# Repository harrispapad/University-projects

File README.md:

# University Projects

This repository contains coursework and projects from my Electrical and Computer Engineering studies at the National Technical University of Athens (NTUA). Each directory represents a different course with assignments, lab work, and projects.

## 📚 Course Overview

### Computer Architecture & Systems

#### [Advanced Computer Architecture](Advanced%20Computer%20Architecture/)

Advanced topics in computer architecture including branch prediction algorithms and memory hierarchy optimization using Intel Pin tools and SPEC CPU2006 benchmarks.

#### [Computer Architecture](Computer%20Architecture/)

Fundamental and advanced computer architecture concepts including ISA, pipelining, cache design, and multiprocessor systems.

#### [Advanced Operational Systems](Advanced%20Operational%20Systems/)

Linux kernel programming, device drivers (LUNIX TNG sensor driver), and system-level programming.

#### [Operational Systems](Operational%20Systems/)

Unix/Linux system programming, process management, POSIX threads, and synchronization primitives.

### VLSI & Hardware Design

#### [Analog VLSI](Analog%20VLSI/)

Analog Bayesian classifier circuit design with winner-take-all circuits, current mirrors, and performance analysis.

#### [Analog System Design](Analog%20System%20Design/)

Phase-Locked Loop (PLL) circuit design with LTspice simulations and KiCad PCB implementation.

#### [Digital VLSI](Digital%20VLSI/)

FPGA design using Xilinx Vivado: decoders, shift registers, BCD adders, systolic multipliers, and Bayer demosaicing for image processing.

#### [Digital Systems Lab](Digital%20Systems%20Lab/)

Digital circuit design using Logisim: clock generators, display circuits, counters, and Pong display systems.

#### [Electrical Design](Electrical%20Design/)

Complete electrical installation design for multi-story buildings using AutoCAD, including floor plans, panel diagrams, and load calculations.

### Programming & Software

#### [Algorithms and Complexity](Algorithms%20and%20Complexity/)

Theoretical and programming assignments covering algorithm design, complexity analysis, graph algorithms, and competitive programming problems.

#### [Compilers](Compilers/)

Complete compiler implementation for the Dana programming language with lexer, parser, semantic analysis, and LLVM IR code generation.

#### [Databases](Databases/)

MasterChef competition management database with ER modeling, MySQL implementation, and automated data population scripts.

#### [Programming Languages](Programming%20Languages/)

Multi-paradigm programming comparing imperative (C/C++), object-oriented (Java), functional (Standard ML), logic (Prolog), and scripting (Python) approaches.

#### [Software Engineering](Software%20Engineering/)

Full-stack web application with Express.js backend, MySQL database, web frontend, and CLI client featuring JWT authentication.

#### [progintro](progintro/)

Introductory C programming: data structures, algorithms, and fundamental programming concepts.

#### [progtech](progtech/)

Advanced C++ programming with focus on STL (Standard Template Library) and object-oriented design.

### Microprocessors & Embedded Systems

#### [Intro to Microprocessors](Intro%20to%20Microprocessors/)

Assembly language programming for 8085 and AVR microprocessors using Atmel Studio.

#### [Microlab](Microlab/)

PIC18 microcontroller programming with MPLAB X: I2C/TWI communication, LCD interfaces, USART, and One-Wire protocols.

### AI & Machine Learning

#### [Neural Networks and Deep Learning](Neural%20Networks%20and%20Deep%20Learning/)

Deep learning implementations in Python/Jupyter: Wide Residual Networks, neural network architectures, and optimization techniques.

## 🛠️ Technologies & Tools

- **Languages**: C, C++, Java, Python, Standard ML, Prolog, VHDL, Assembly (8085, AVR, PIC18), JavaScript, SQL
- **Hardware Design**: Xilinx Vivado, LTspice, KiCad, Logisim, AutoCAD, Logisim
- **Development Tools**: Intel Pin, MPLAB X, Atmel Studio, MySQL Workbench
- **Frameworks**: Express.js, Node.js, LLVM, PyTorch/TensorFlow
- **Version Control**: Git

## 📁 Repository Structure

Each course directory contains:

- Assignment descriptions and requirements
- Source code and implementations
- Project reports and documentation
- Test cases and validation scripts
- Build configurations and makefiles

## 📖 Documentation

Each subdirectory has its own README with detailed information about:

- Course objectives and learning outcomes
- Assignment descriptions and solutions
- Implementation details and design decisions
- Tools and technologies used

## 🎓 Institution

**National Technical University of Athens (NTUA)**
School of Electrical and Computer Engineering

---

*This repository serves as a comprehensive portfolio of my academic work in Electrical and Computer Engineering.*

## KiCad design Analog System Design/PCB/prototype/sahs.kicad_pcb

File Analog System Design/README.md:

# Analog System Design

This directory contains the course project for Analog System Design, focused on designing and implementing a Phase-Locked Loop (PLL) system.

## Contents

### Project Overview

Design and implementation of a complete PLL (Phase-Locked Loop) circuit, including:

- VCO (Voltage-Controlled Oscillator) design
- Phase detector implementation
- Loop filter design
- Complete PLL system integration

**Partners:** Chronopoulos Stefanos, Gougousi Ioanna

Simulations (`simulations/`)

LTspice simulation files for circuit analysis and verification:

- VCO simulations and small-signal analysis
- Complete PLL system simulations
- Parametric sweeps and performance analysis
- Simulation logs and results documentation

### PCB Design (`PCB/`)

KiCad PCB design files for physical implementation:

- Custom component footprints for ICs (74HC00, 74HC14, 74HCT74, LM324) and transistors (2N2222, 2N2907)
- Schematic symbols library
- PCB layouts (prototype and final with switch)
- SPICE models for circuit simulation in KiCad

### Documentation

- **`report.pdf`**: Final project report

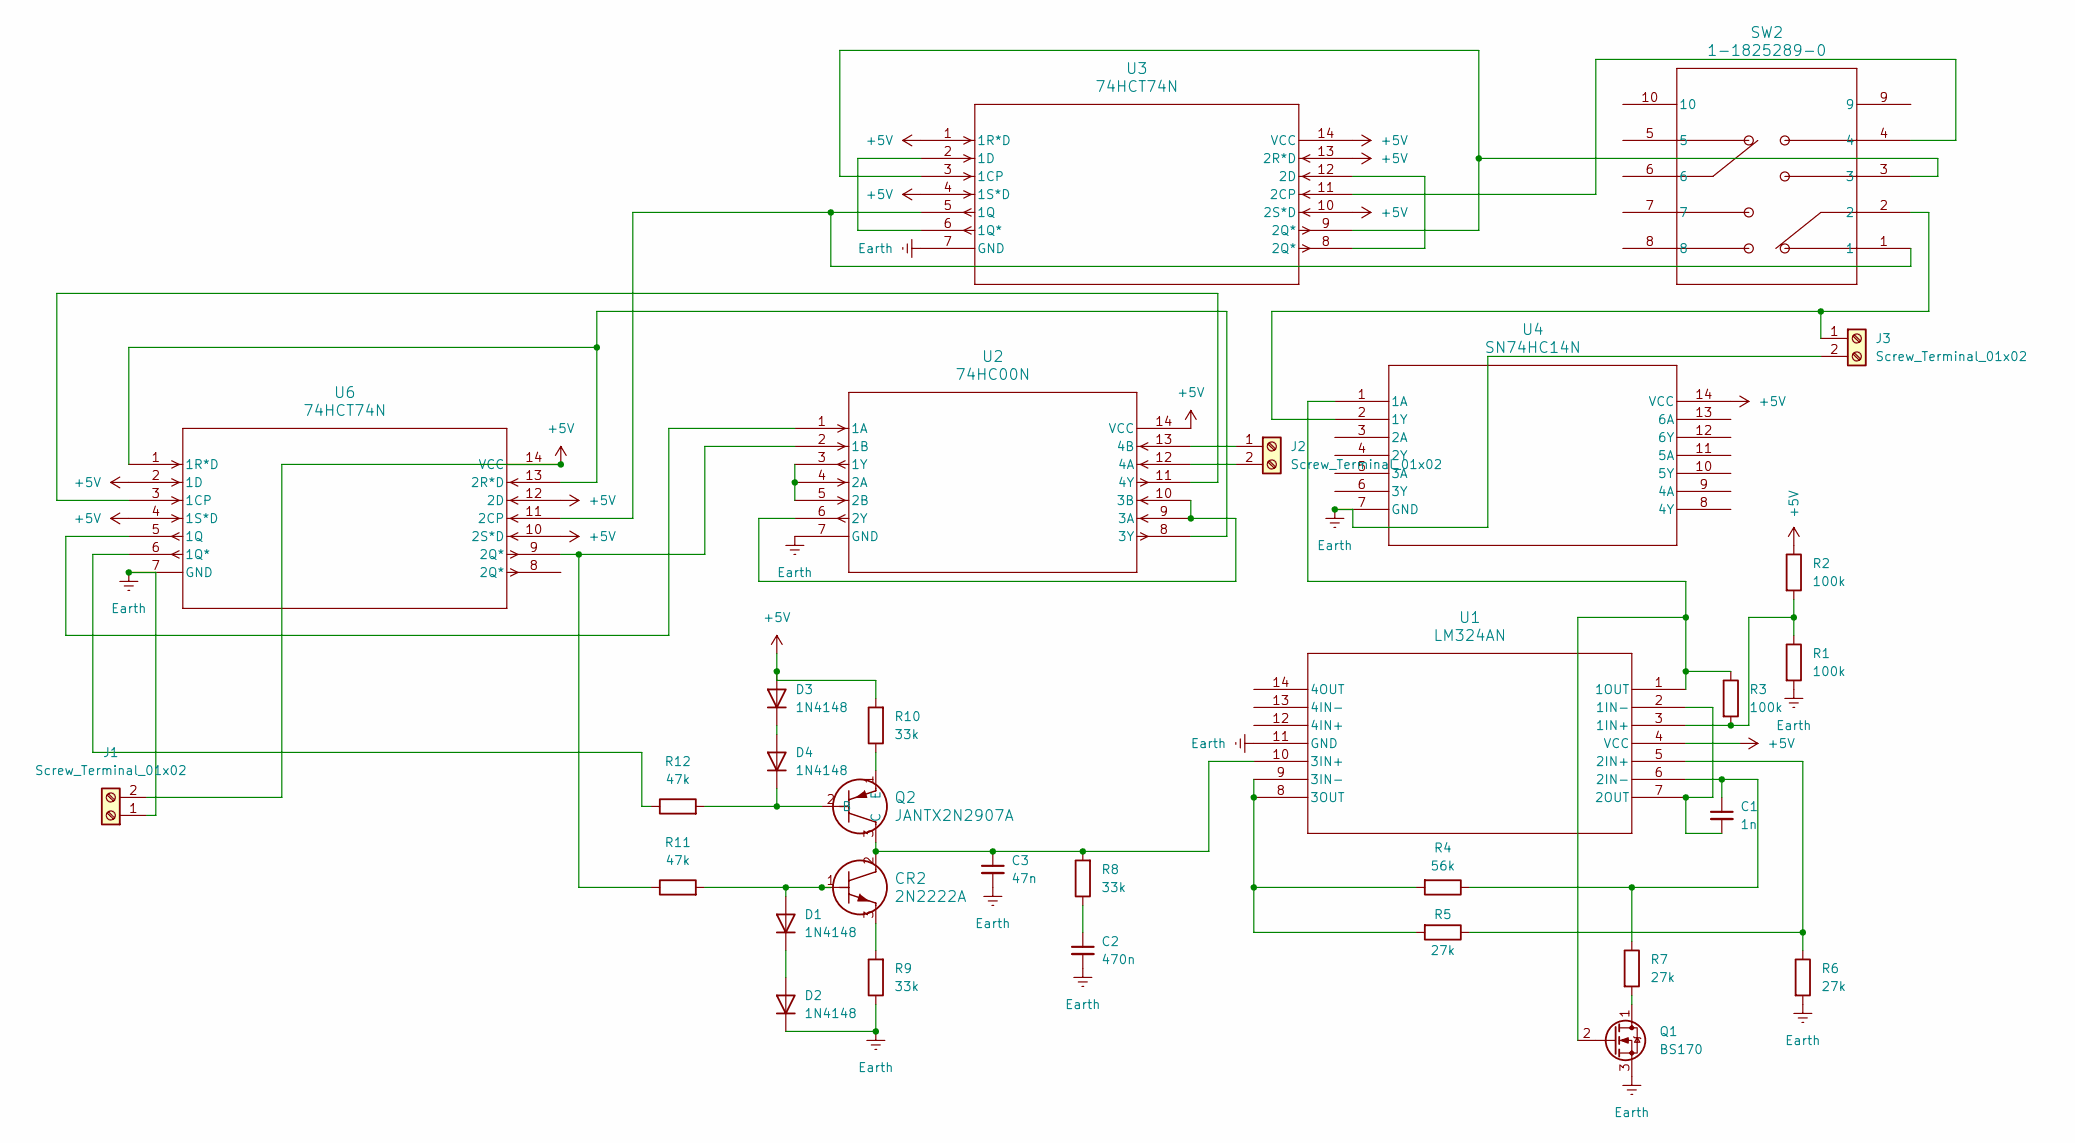
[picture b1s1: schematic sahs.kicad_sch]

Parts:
C1: 1n; C_Disc_D3.0mm_W1.6mm_P2.50mm
C2: 470n; C_Rect_L7.0mm_W6.0mm_P5.00mm
C3: 47n; C_Disc_D3.0mm_W1.6mm_P2.50mm
CR2: 2N2222A; TO-18_STM
D1, D2, D3, D4: 1N4148; D_DO-35_SOD27_P7.62mm_Horizontal
J1, J2, J3: Screw_Terminal_01x02; TerminalBlock_Altech_AK300-2_P5.00mm
Q1: BS170; TO-92_Inline
Q2: JANTX2N2907A; TO-18TO-206AA_MCH
R1, R2, R3: 100k; R_Axial_DIN0207_L6.3mm_D2.5mm_P7.62mm_Horizontal
R4: 56k; R_Axial_DIN0207_L6.3mm_D2.5mm_P7.62mm_Horizontal
R5, R6, R7: 27k; R_Axial_DIN0207_L6.3mm_D2.5mm_P7.62mm_Horizontal
R8, R9, R10: 33k; R_Axial_DIN0207_L6.3mm_D2.5mm_P7.62mm_Horizontal
R11, R12: 47k; R_Axial_DIN0207_L6.3mm_D2.5mm_P7.62mm_Horizontal
SW2: 1-1825289-0; SW8_MHS233_TEC
U1: LM324AN; N14
U2: 74HC00N; SOT27-1_NEX
U3, U6: 74HCT74N; SOT27-1_NEX
U4: SN74HC14N; N14

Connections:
+5V: D3.2 (A), J1.2, R2.1, R10.2, U1.4 (VCC), U2.14 (VCC), U3.1 (1R*D), U3.4 (1S*D), U3.10 (2S*D), U3.13 (2R*D), U3.14 (VCC), U4.14 (VCC), U6.2 (1D), U6.4 (1S*D), U6.10 (2S*D), U6.12 (2D), U6.14 (VCC)
Earth: C2.2, C3.2, D2.1 (K), J1.1, J3.2, Q1.3 (S), R1.2, R6.2, R9.1, U1.11 (GND), U2.7 (GND), U3.7 (GND), U4.7 (GND), U6.7 (GND); also elsewhere on the board
unnamed: C2.1, R8.1
unnamed: CR2.3, R9.2
unnamed: CR2.1, D1.2 (A), R11.2
unnamed: D1.1 (K), D2.2 (A)
unnamed: D3.1 (K), D4.2 (A)
unnamed: D4.1 (K), Q2.2 (B), R12.2
unnamed: J2.1, U2.13 (4B)
unnamed: J2.2, U2.12 (4A)
unnamed 10: Q1.1 (D), R7.2; also elsewhere on the board
unnamed 11: Q1.2 (G), R3.1, U1.1 (1OUT), U4.1 (1A); also elsewhere on the board
unnamed: C3.1, CR2.2, Q2.3 (C), R8.2, U1.10 (3IN+)
unnamed: Q2.1 (E), R10.1
unnamed: R1.1, R2.2, R3.2, U1.3 (1IN+)
unnamed: C1.2, U1.2 (1IN-), U1.7 (2OUT)
unnamed: R5.1, R6.1, U1.5 (2IN+)
unnamed: C1.1, R4.1, R7.1, U1.6 (2IN-)
unnamed: R4.2, R5.2, U1.8 (3OUT), U1.9 (3IN-)
unnamed: U2.1 (1A), U6.5 (1Q)
unnamed: R11.1, U2.2 (1B), U6.9 (2Q*)
unnamed: U2.3 (1Y), U2.4 (2A), U2.5 (2B)
unnamed: U2.6 (2Y), U2.9 (3A), U2.10 (3B)
unnamed: U2.8 (3Y), U6.1 (1R*D), U6.13 (2R*D)
unnamed: U2.11 (4Y), U6.3 (1CP)
unnamed: SW2.3, U3.3 (1CP), U3.9 (2Q*)
unnamed: U3.2 (1D), U3.6 (1Q*)
unnamed: SW2.1, U3.5 (1Q), U6.11 (2CP)
unnamed: U3.8 (2Q*), U3.12 (2D)
unnamed: R12.1, U6.6 (1Q*)

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
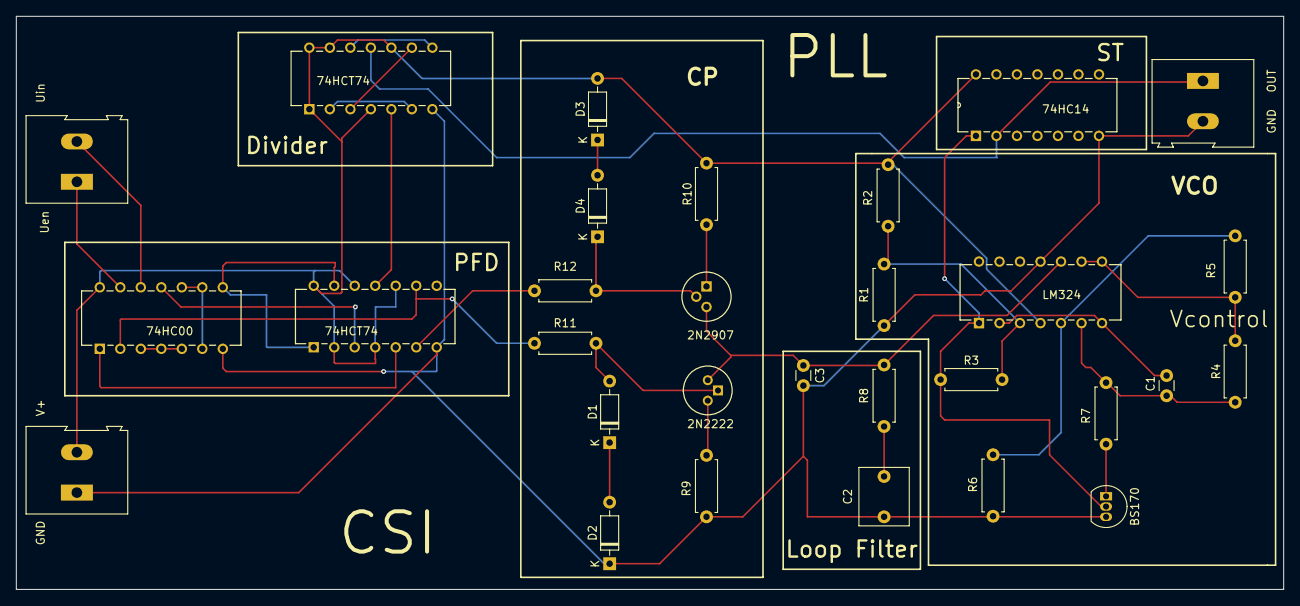
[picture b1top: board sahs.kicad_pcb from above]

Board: 2 copper layers, 157.0 x 71.0 mm, 30 parts (0 on the bottom side), 31 nets.

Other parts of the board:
BS170: BS170; TO-92_Inline

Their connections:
Earth: BS170.3 (S); also elsewhere on the board
unnamed 10: BS170.1 (D); also elsewhere on the board
unnamed 11: BS170.2 (G); also elsewhere on the board

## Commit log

2025-10-03 Upload projects
